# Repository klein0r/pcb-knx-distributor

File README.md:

# KNX Distributor

Just a simple PCB to distribute the KNX bus (for development / testing)

[Gerber-Files](https://github.com/klein0r/pcb-knx-distributor/releases)

## Preview

## Parts

- 28x Wago 243-131
- 7x Wago 243-211 (red/black)
- 7x Wago 243-212 (yellow/grey)

```* = Affiliate Link```

## License

The MIT License (MIT)

Copyright (c) 2026 Matthias Kleine <info@haus-automatisierung.com>

Permission is hereby granted, free of charge, to any person obtaining a copy
of this software and associated documentation files (the "Software"), to deal
in the Software without restriction, including without limitation the rights
to use, copy, modify, merge, publish, distribute, sublicense, and/or sell
copies of the Software, and to permit persons to whom the Software is
furnished to do so, subject to the following conditions:

The above copyright notice and this permission notice shall be included in
all copies or substantial portions of the Software.

THE SOFTWARE IS PROVIDED "AS IS", WITHOUT WARRANTY OF ANY KIND, EXPRESS OR
IMPLIED, INCLUDING BUT NOT LIMITED TO THE WARRANTIES OF MERCHANTABILITY,
FITNESS FOR A PARTICULAR PURPOSE AND NONINFRINGEMENT. IN NO EVENT SHALL THE
AUTHORS OR COPYRIGHT HOLDERS BE LIABLE FOR ANY CLAIM, DAMAGES OR OTHER
LIABILITY, WHETHER IN AN ACTION OF CONTRACT, TORT OR OTHERWISE, ARISING FROM,
OUT OF OR IN CONNECTION WITH THE SOFTWARE OR THE USE OR OTHER DEALINGS IN
THE SOFTWARE.

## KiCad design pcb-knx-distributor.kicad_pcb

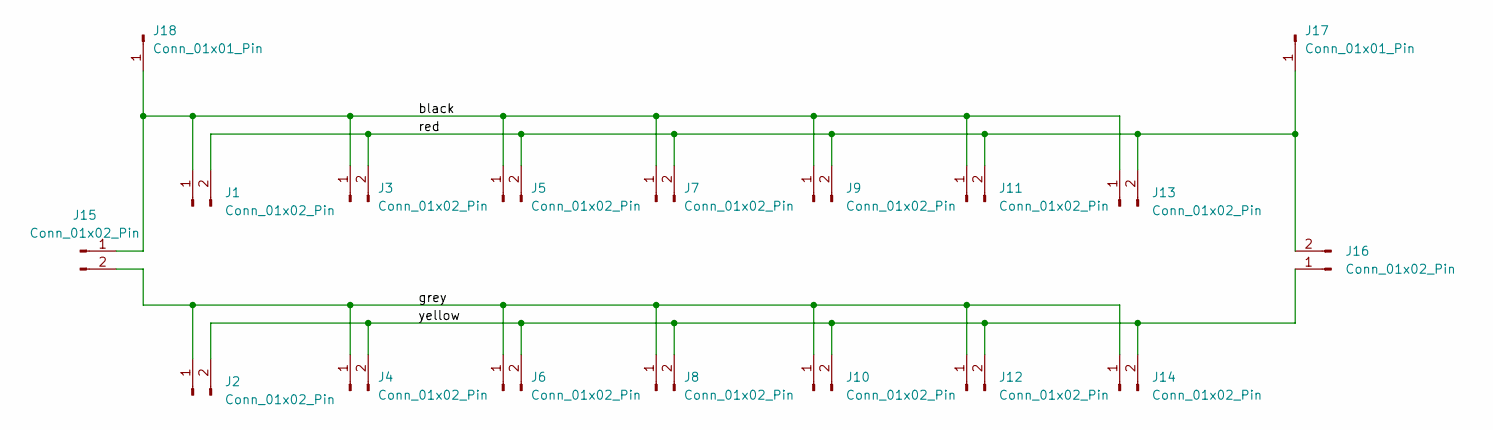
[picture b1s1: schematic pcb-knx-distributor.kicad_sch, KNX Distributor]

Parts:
J1, J3, J5, J7, J9, J11, J13: Conn_01x02_Pin; Wago-243-211
J2, J4, J6, J8, J10, J12, J14: Conn_01x02_Pin; Wago-243-212
J15, J16: Conn_01x02_Pin; PinHeader_2x01_P2.54mm_Vertical
J17, J18: Conn_01x01_Pin; PinHeader_1x01_P2.54mm_Vertical

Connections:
/black: J1.1, J3.1, J5.1, J7.1, J9.1, J11.1, J13.1, J15.1, J18.1 (Pin_1_1)
/grey: J2.1, J4.1, J6.1, J8.1, J10.1, J12.1, J14.1, J15.2
/red: J1.2, J3.2, J5.2, J7.2, J9.2, J11.2, J13.2, J16.2, J17.1 (Pin_1_1)
/yellow: J2.2, J4.2, J6.2, J8.2, J10.2, J12.2, J14.2, J16.1

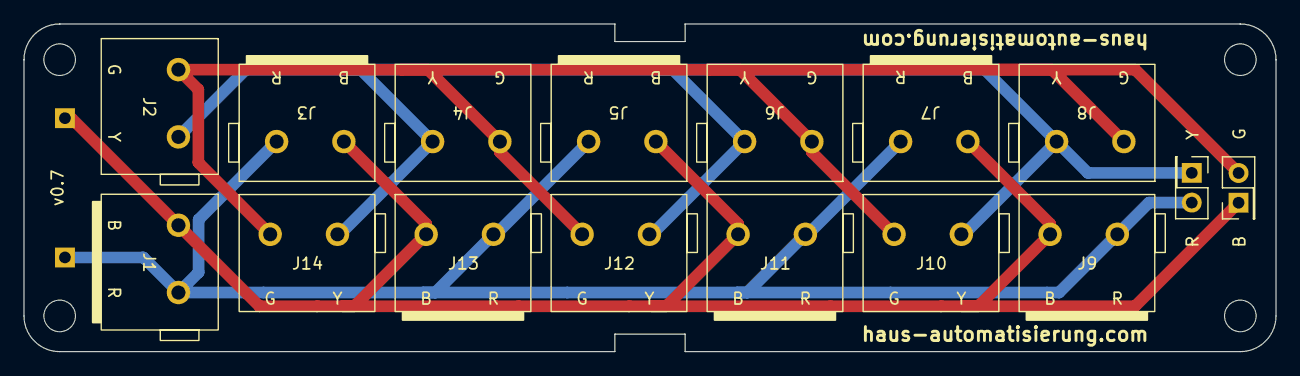
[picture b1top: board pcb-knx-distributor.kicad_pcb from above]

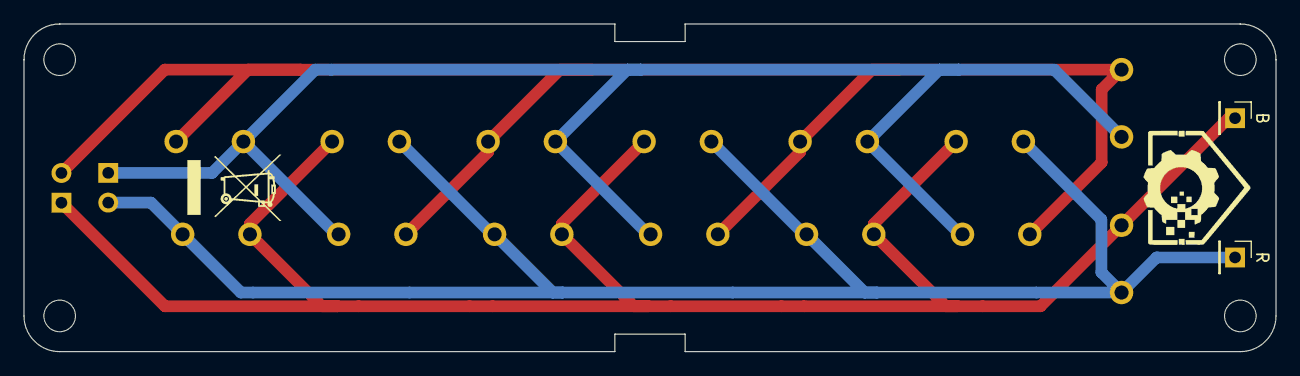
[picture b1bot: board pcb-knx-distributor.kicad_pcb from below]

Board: 2 copper layers, 107.0 x 28.0 mm, 18 parts (2 on the bottom side), 4 nets.

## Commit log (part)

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2023-08-15 Fixed preview url
2023-08-15 Parts
2023-08-15 Tracks on both sides
2023-08-15 Updated footprints
2023-08-15 Enlarged PCB
2023-08-22 Added photo
2024-02-21 v0.3
2024-03-08 v0.5
2024-04-30 KiCad 8
2024-05-31 v0.6
2026-01-28 Year 2026

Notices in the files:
parts and their libraries:
STEP files are licensed under CC BY-ND 4.0 by PartsCommunity / PARTsolutions / CADENAS
